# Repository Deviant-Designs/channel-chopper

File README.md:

# Channel-Chopper
A Fire button for any estim device. Perfect for BDSM play 

## Quick Disclaimer
I am neither an electrical engineer or a software developer. I made this for fun. There are probably many many flaws in this. But that being said, it works and works well for what I want. I don't mind constructive critiscm at all (actually I'll be greatful for it) but please be nice with it. It sucks when you put lots of effort into something and people just hammer it for its flaws :)

## What is it
this is a inline controller to turn on and off estim signals. You attach it between the estim unit and the bipolar electrode. it has 4 buttons on it which when depressed allow the estim signals to passthrough to the electrodes. It also works via serial comunication so you can link it up to other equipment if you wish. 

## You said 4 Channels, Why 5 inputs/Outputs?
channel 5 in the channel chopper is actually controlled by channel 4. the idea behind this is if you have 2 bipolar nipple clamps. One on each nipple. If you press the channel 4 button they will both fire at the same time

## BOM
11 - 3.5mm Panel Mount Stereo Jacks

10 - MOC 3023

1 - Arduino Pro Micro (it has to be micro not mini for this PCB)

14 - 220Ω Resistors

4 - 5mm LEDS

4 - Buttons/swtiches

## Serial Format
This is done through the USB cable. Basic serial comunication at 9600. The format is as follows

`shock¬"channel"¬"state"`

There are 4 channels and the states are either `1` for on or `0` for off. So if we wanted to turn channel 2 on we would send

`shock¬2¬1`

and if we wanted to turn channel 2 off it would be 

`shock¬2¬0`

## why is there another serial connection linked to a 3.5mm jack
this hasn't been implemented in software yet, but I put this there in case I wanted to setup software serial to control the box from another arduino. or maybe use this box to trigger other devices. The tip is connected to pin A1 and the ring to A0

## Thankyou's 
I need to say thanks to both Georgexx and Onwrikbaar as they showed me the light with the MOC3023's

## Links
[Discord](https://discord.gg/6kjEPdq)

If you like what we do and want to support us then please consider the following options

[Patreon](https://www.patreon.com/deviantdesigns)

[Ko-Fi - if you'd rather a one off donation](https://www.Ko-fi.com/deviantdesigns)

[Twitter - sharing our work helps lots too if you can't afford to support financially](https://twitter.com/_DeviantDesigns)

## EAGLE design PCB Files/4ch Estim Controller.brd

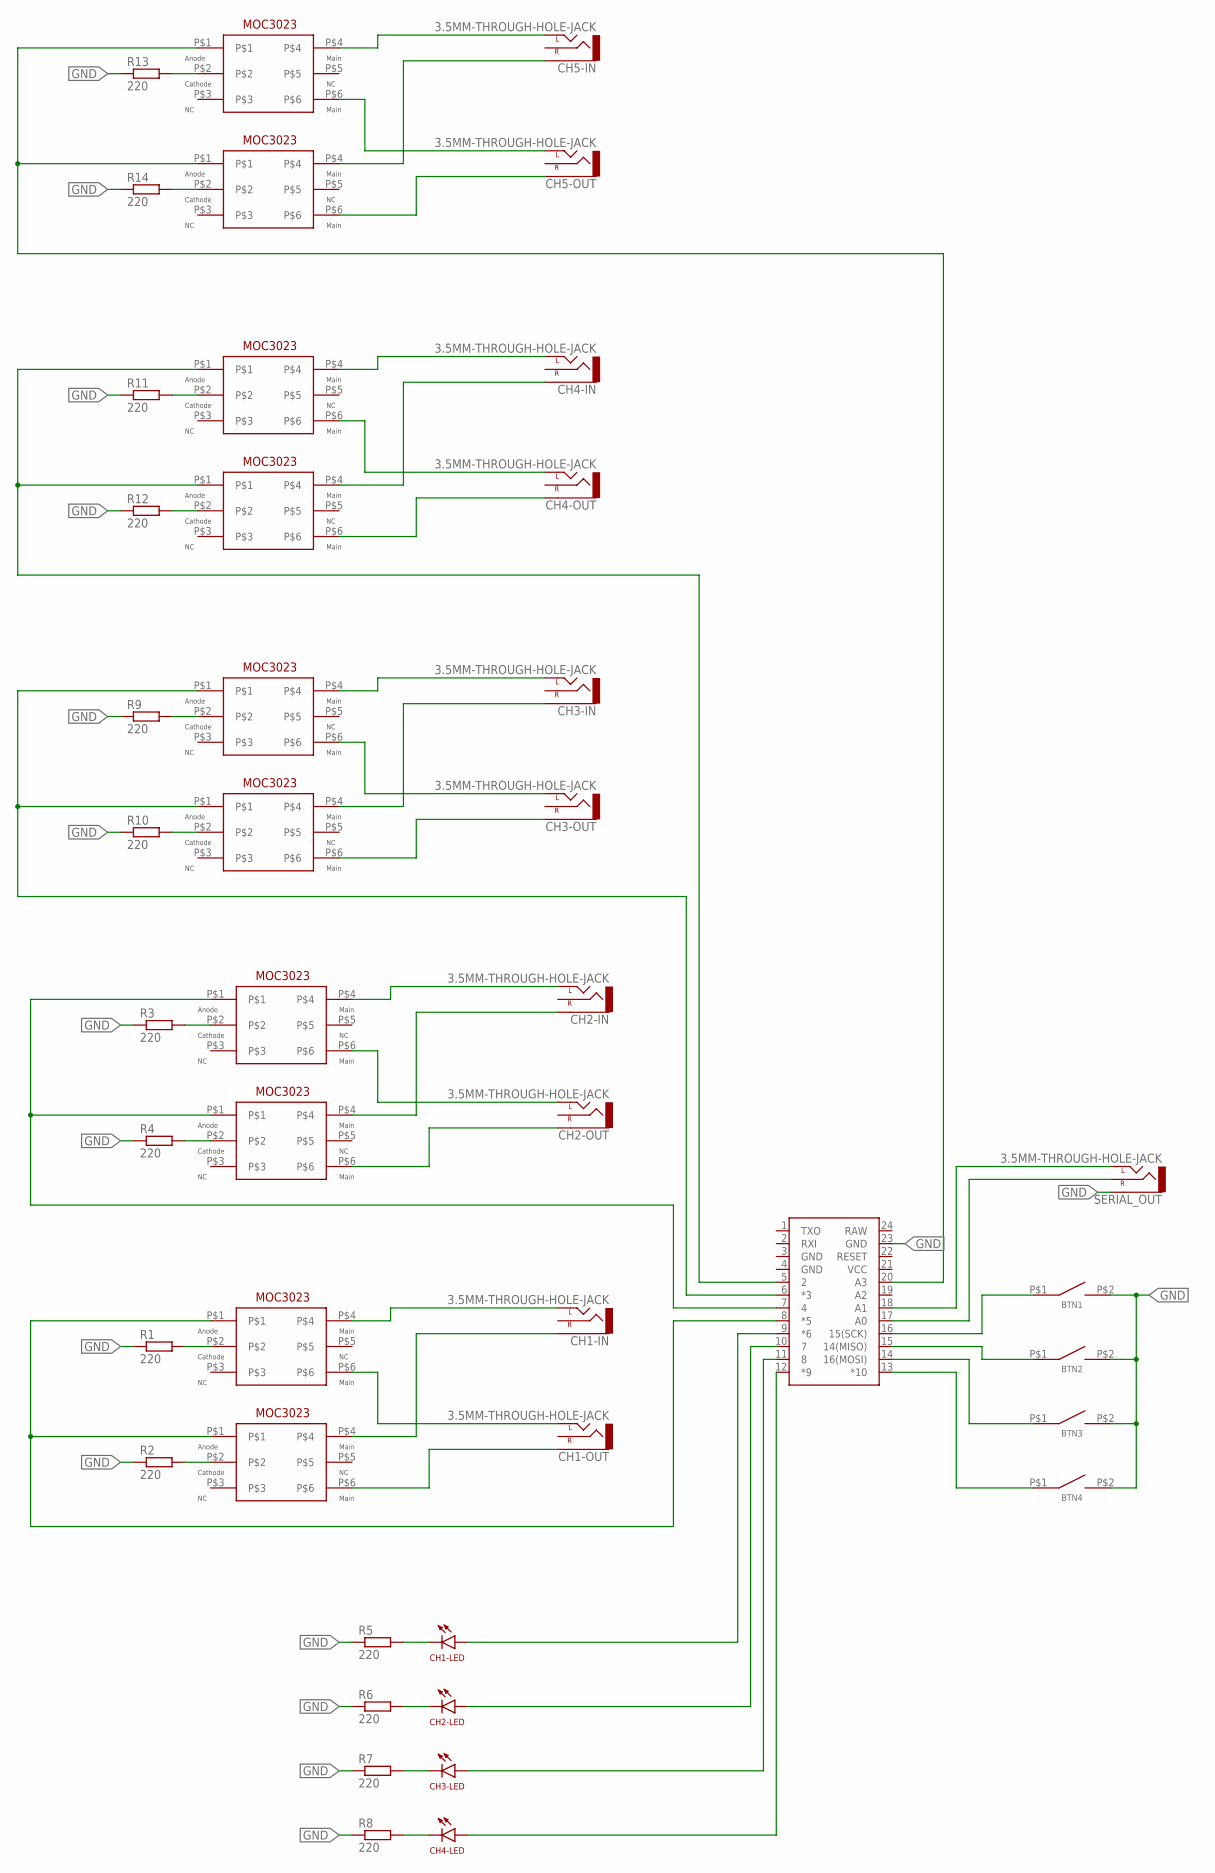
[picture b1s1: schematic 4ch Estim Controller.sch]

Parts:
B1: PRO_MICRO
BTN1, BTN2, BTN3, BTN4: THROUGH-HOLE-SWITCH
CH1-IN, CH1-OUT, CH2-IN, CH2-OUT, CH3-IN, CH3-OUT, CH4-IN, CH4-OUT, CH5-IN, CH5-OUT: 3.5MM-THROUGH-HOLE-JACK; THROUGH-HOLE-JACK
CH1-LED, CH2-LED, CH3-LED, CH4-LED: THROUGH-HOLE-LED
R1, R2, R3, R4, R5, R6, R7, R8, R9, R10, R11, R12, R13, R14: 220; 0207/10
SERIAL_OUT: 3.5MM-THROUGH-HOLE-JACK; THROUGH-HOLE-JACK
U$1, U$2, U$3, U$4, U$9, U$10, U$11, U$12, U$13, U$14: MOC3023

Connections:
GND: B1.3 (GND), B1.4 (GND), B1.23 (GND), BTN1.P$2, BTN2.P$2, BTN3.P$2, BTN4.P$2, R1.1, R2.1, R3.1, R4.1, R5.1, R6.1, R7.1, R8.1, R9.1, R10.1, R11.1, R12.1, R13.1, R14.1, SERIAL_OUT.P$3 (SLEEVE)
unnamed: B1.13 (*10), BTN4.P$1
unnamed: B1.14 (16(MOSI)), BTN3.P$1
unnamed: B1.15 (14(MISO)), BTN2.P$1
unnamed: B1.16 (15(SCK)), BTN1.P$1
unnamed: CH1-IN.P$1 (LEFT), U$3.P$4
unnamed: CH1-LED.P$2 (C), R5.2
unnamed: CH2-LED.P$2 (C), R6.2
unnamed: CH3-LED.P$2 (C), R7.2
unnamed: CH4-LED.P$2 (C), R8.2
unnamed: B1.12 (*9), CH4-LED.P$1 (A)
unnamed: B1.11 (8), CH3-LED.P$1 (A)
unnamed: B1.10 (7), CH2-LED.P$1 (A)
unnamed: B1.9 (*6), CH1-LED.P$1 (A)
unnamed: CH1-IN.P$3 (SLEEVE), U$4.P$4
unnamed: R2.2, U$4.P$2
unnamed: R1.2, U$3.P$2
unnamed: B1.8 (*5), U$3.P$1, U$4.P$1
unnamed: CH1-OUT.P$1 (LEFT), U$3.P$6
unnamed: CH1-OUT.P$3 (SLEEVE), U$4.P$6
unnamed: CH2-IN.P$1 (LEFT), U$1.P$4
unnamed: CH2-IN.P$3 (SLEEVE), U$2.P$4
unnamed: CH2-OUT.P$1 (LEFT), U$1.P$6
unnamed: B1.17 (A0), SERIAL_OUT.P$2 (RIGHT)
unnamed: B1.18 (A1), SERIAL_OUT.P$1 (LEFT)
unnamed: CH2-OUT.P$3 (SLEEVE), U$2.P$6
unnamed: B1.7 (4), U$1.P$1, U$2.P$1
unnamed: R4.2, U$2.P$2
unnamed: R3.2, U$1.P$2
unnamed: CH3-IN.P$1 (LEFT), U$9.P$4
unnamed: CH3-IN.P$3 (SLEEVE), U$10.P$4
unnamed: CH3-OUT.P$1 (LEFT), U$9.P$6
unnamed: CH3-OUT.P$3 (SLEEVE), U$10.P$6
unnamed: B1.6 (*3), U$9.P$1, U$10.P$1
unnamed: R9.2, U$9.P$2
unnamed: R10.2, U$10.P$2
unnamed: CH4-IN.P$1 (LEFT), U$11.P$4
unnamed: CH4-IN.P$3 (SLEEVE), U$12.P$4
unnamed: CH4-OUT.P$1 (LEFT), U$11.P$6
unnamed: CH4-OUT.P$3 (SLEEVE), U$12.P$6
unnamed: B1.5 (2), U$11.P$1, U$12.P$1
unnamed: R11.2, U$11.P$2
unnamed: R12.2, U$12.P$2
unnamed: CH5-IN.P$1 (LEFT), U$13.P$4
unnamed: CH5-IN.P$3 (SLEEVE), U$14.P$4
unnamed: CH5-OUT.P$1 (LEFT), U$13.P$6
unnamed: CH5-OUT.P$3 (SLEEVE), U$14.P$6
unnamed: R13.2, U$13.P$2
unnamed: R14.2, U$14.P$2
unnamed: B1.20 (A3), U$13.P$1, U$14.P$1
RAW: B1.24 (RAW)
VCC: B1.21 (VCC)

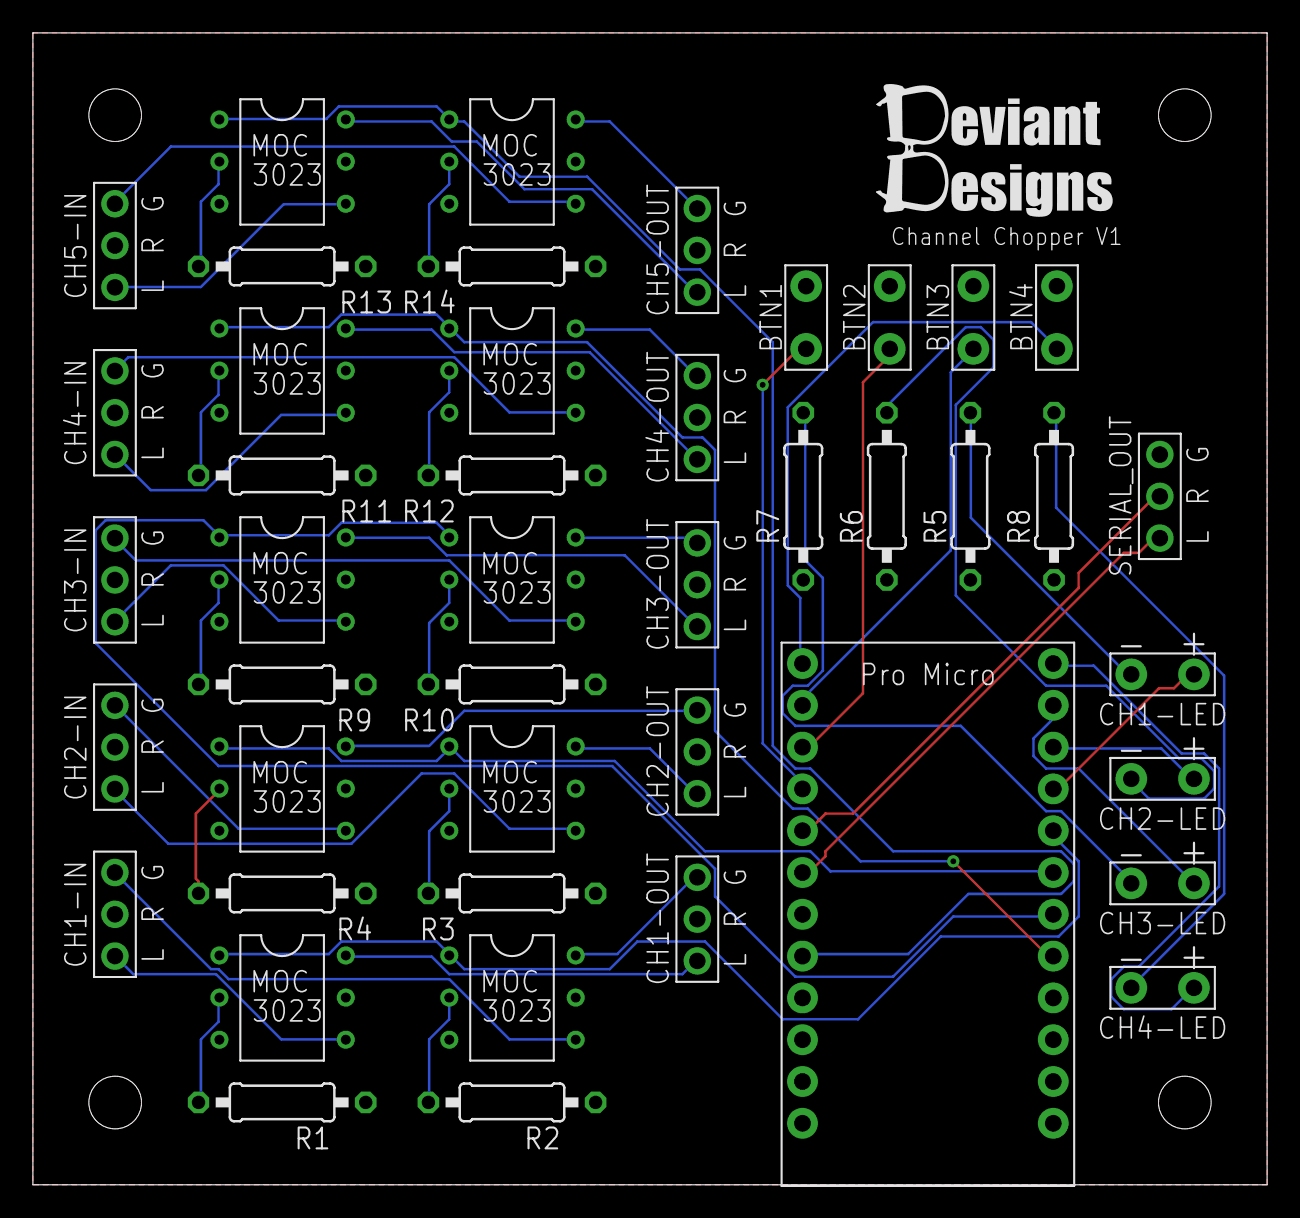
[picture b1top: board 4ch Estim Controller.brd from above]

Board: 2 copper layers, 75.0 x 70.0 mm, 45 parts (0 on the bottom side), 50 nets.

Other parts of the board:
U$15: LOGO_DD_10MM_HIGH

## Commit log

2019-07-26 Added Schematic.png
